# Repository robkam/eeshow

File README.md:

# eeshow
Eeshow - Eeschema schematics renderer and viewer, a tool to ease KiCad schematic file navigation.

Forked from http://neo900.org/stuff/eeshow/.

See https://github.com/robkam/eeshow/wiki for more info.

In the transition between KiCad 4 and KiCad 5 the savefiles format has changed the way libraries are looked up. So Eeshow now needs an update to support both versions.

This work is distributed under the terms of the GNU GENERAL PUBLIC LICENSE, Version 2.

Folder eeshow is eeshow.

Folder ee is the Neo900 schematics, refered to as an example in the wiki.

Folder img is images for the wiki.

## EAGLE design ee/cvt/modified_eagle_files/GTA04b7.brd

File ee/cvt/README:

Conversion session transcript
=============================

git clone https://github.com/lachlanA/eagle-to-kicad.git
mkdir <base-directory>
cd <base-directory>
mkdir eagle
cp ../gdc/sep18/* eagle
mkdir cvt

Some of the following interactions are timestamped, to indicate roughly
when to expect interactions. The timestamps are [minutes:seconds] of
total CPU time of the "eagle" process on a Q6600.

Note: it is best not type anything else during the conversion, especially
around the time when new dialogs may pop up. The Eagle pop-ups will appear
unannounced and grab the input focus. Keystrokes will therefore end up in
Eagle dialogs, changing inputs.

- open schematics in Eagle

File > Run ULP (.../eagle-to-kicad/renumber-sheet.ulp)
- set script path to .../eagle-to-kicad/
- set output directory (.../cvt/)

[10:54] "This ULP will change unconnected VIA's to PADS"
- accept defaults

[11:01] "Consult log file for unncontded via's and tracks"
/home/n9/ee/cvt/GTA04b7_conversion_log.txt
- 1469 unconnected tracks
- 6 unconnected vias
- accept

[11:01] /home/n9/ee/cvt/modified_eagle_files/GTA04b7~fix_via_hack.scr, Line 85:
The Light edition of EAGLE can't perform the requested action!
You can't add parts to this sheet.
- accept
- idem, lines 89, 93, 97, 101, 105. accept.

[11:04] Unknown element VP_0
line 11889
- accept
- idem, VP_1, VP_2, VP_3, VP_4, VP_5. accept.

[11:10] Large dialog
- Output: set all sheet sizes to A3
- Sheet size: set to A3
- accept

[32:11] Library dialog
- Accept (note: dialog stays open after clicking "OK")

[33:21] "There were Errors during the export please read the log for more
	 information"
- Accept

[33:44] /home/n9/ee/cvt/GTA04b7.scr, Line 31320:
Package SOT223-6 doesn't have enough pads for
all 10 pins of device TPS73733
- accept

[33:44] /home/n9/ee/cvt/GTA04b7.scr, Line 31321:
Use the PACKAGE command to select a package variant first
- accept
- idem, lines 31322 to 31326. Accept.

[33:46] Output ... dialog.
- accept defaults

[33:55] There are: 217 missing part prefix(s).
	Conversion finished!
- accept

[33:56] Log file dialog
- accept

Common issues in converted schematics
=====================================

Component text size
-------------------

Component text (component reference, value, etc.), should have a size
of 50 mil. The converted schematics frequently use 45 mil or 70 mil.

KiCad stores the default size, location, and alignment of text fields
in the definition of the schematics symbol ("component", .lib). This
is copied into the schematics when placing a symbol, and can then be
modified individually for each use of the symbol.

To change a symbol in the library, right-click on the symbol in the
schematics, Edit component > Edit with Library Editor
Make the changes in the component editor. Important: make sure that
all pins are aligned with a 50 mil grid. To abort changes, simply
quit the component editor. To save changes, click
Update current component in current library
followed by
Save current library to disk

Eeschema will pick up changes in geometry and fixed text automatically,
but it will not change fields of existing symbols. To update fields to
the definitions in the library, press E to edit the component, then
click Reset to Library Defaults.

Component text alignment
------------------------

Many text fields in the converted schematics are vertically aligned
with the bottom of the text. It is often more convenient to align with
the center, such that a field can be placed near a wire (or anything
else that follows the 50 mil grid) without getting too close.

Pin types
---------

Some pin types in the converted schematics are incorrect or at least
unusual. In general, passive components like LED should have their
terminals marked as "passive", not as "power input" or such.

Pin types can only be corrected by changing the component in the
library.

Label text size
---------------

Many labels have (or had) a text size of 65 mil. This makes global
labels overlap when stacked with 100 mil spacing. The text size can
be changed by pressing "E" on the label.

Label type and direction
------------------------

Labels that should be global were converted to local. To change them
back to global, right-click, Change type > Change to Global Label

In KiCad, global and hierarchical labels (but not local labels)
indicate a direction. This can be changed by pressing "E" on the global
label.

Tiny labels
-----------

The converter flags each net with a tiny label (10 mil), to ensure the
net is really what Eagle said it was. Most of these labels have already
been removed, but some remain.

In general, all such labels should be deleted. Since they can sometimes
indicate conflicts in the design (cf. VBUS), one should check, before
deleting, that they are consistent with the net that is expected to be
at this location.

Power flag
----------

KiCad requires all nets that are used as power input to be driven by a
power output (i.e., a pin marked as such). If a net has no implicit
power source (e.g., if it is separated from a power output by a choke),
the POWERED symbol (which is a single-pin power output) has to be placed
on the net. (POWERED is a nicer form of PWR_FLAG from the default KiCad
library.)

Unusual wiring
--------------

The "normal" drawing style in KiCad is that pins are connected by a
single wire that continues for at least 50 mil, better 100 mil, in the
direction of the pin. This wire can then bend, form T-joints with other
wires, etc.

The converted schematics contain a large number of wires that are
perpendicular to the pin they connect to, and some pins are even
connected directly, without wire. While this "works", it often looks
confusing and it complicates moving or dragging items. The best way to
resolve such issues is often to just delete the wires and junctions of
the net in question, move components to create a bit more room, then
redraw the net.

Caution: deleting a wire often deletes the entire wire, across
junctions. Checking the result of major reconstruction against a PDF
taken from the original state (or the Eagle original) is recommended.

Unifying multi-unit components
------------------------------

Some components are drawn as consisting of a very large number of
units. E.g., the rather simple digital microphones had no less than
five units each.

A quick way to reduce the number of units is to invoke the component
editor on the component, setting the pins in units B and above to
"Common to all units in component", reducing the number of units in
"Edit component properties" to one, and finally arranging the pins in
a suitable pattern.

Oversized arcs
--------------

KiCad arcs can be either clockwise or counter-clockwise, and there is
no explicit indication of the direction. To avoid ambiguities, arcs are
limited to < 180 degrees. The converter seems to be unaware of this
restriction and produces arcs >= 180 degrees. (Even when drawing an arc
of 180 degrees in KiCad, it is saved with a start and end angle of 0.1
and 179.9 degrees, respectively.)

To fix this, oversized each arc needs to be broken into two (or more)
smaller arcs.

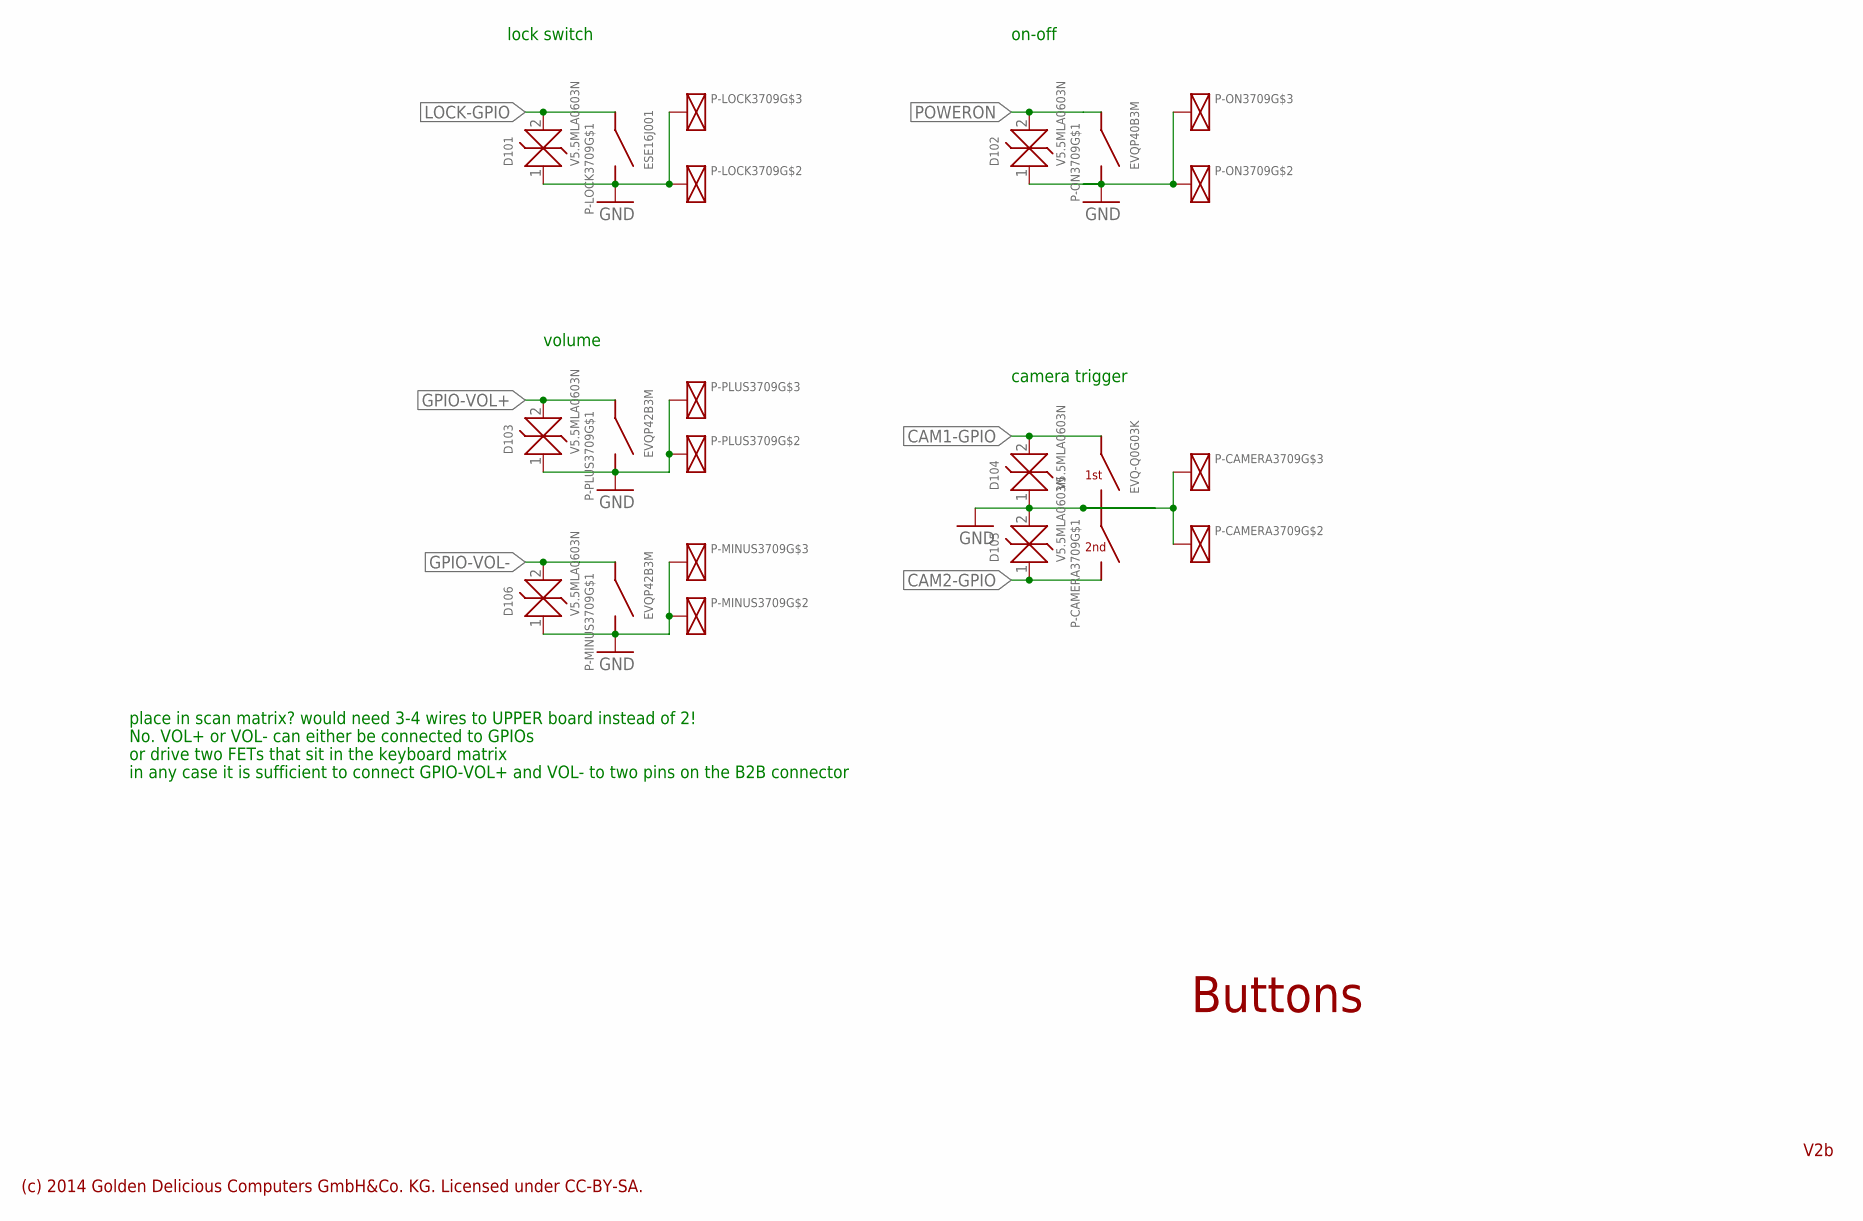
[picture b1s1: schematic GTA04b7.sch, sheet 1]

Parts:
D101, D102, D103, D104, D105, D106: V5.5MLA0603N; SMD-0603
P-CAMERA3709: EVQ-Q0G03K; EVQQ0
P-LOCK3709: ESE16J001; ESE-16J001
P-MINUS3709: EVQP42B3M; EVQP40B3M
P-ON3709: EVQP40B3M
P-PLUS3709: EVQP42B3M; EVQP40B3M

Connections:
CAM1-GPIO: D104.2 (K), P-CAMERA3709.1
CAM2-GPIO: D105.1 (A), P-CAMERA3709.2
GND: D101.1 (A), D102.1 (A), D103.1 (A), D104.1 (A), D105.2 (K), D106.1 (A), P-CAMERA3709.3, P-CAMERA3709.S1 (SHIELD), P-CAMERA3709.S2 (SHIELD), P-LOCK3709.2 (SHIELD), P-LOCK3709.3 (B), P-LOCK3709.4 (SHIELD), P-MINUS3709.2 (B), P-MINUS3709.S1 (SHIELD), P-MINUS3709.S2 (SHIELD), P-ON3709.2 (B), P-ON3709.S1 (SHIELD), P-ON3709.S2 (SHIELD), P-PLUS3709.2 (B), P-PLUS3709.S1 (SHIELD), P-PLUS3709.S2 (SHIELD); also elsewhere on the board
GPIO-VOL+: D103.2 (K), P-PLUS3709.1 (A)
GPIO-VOL-: D106.2 (K), P-MINUS3709.1 (A)
LOCK-GPIO: D101.2 (K), P-LOCK3709.1 (A)
POWERON: D102.2 (K), P-ON3709.1 (A)

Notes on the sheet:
Buttons
(c) 2014 Golden Delicious Computers GmbH&Co. KG. Licensed under CC-BY-SA.
lock switch
on-off
volume
camera trigger
place in scan matrix? would need 3-4 wires to UPPER board instead of 2!
No. VOL+ or VOL- can either be connected to GPIOs
or drive two FETs that sit in the keyboard matrix
in any case it is sufficient to connect GPIO-VOL+ and VOL- to two pins on the B2B connector
V2b

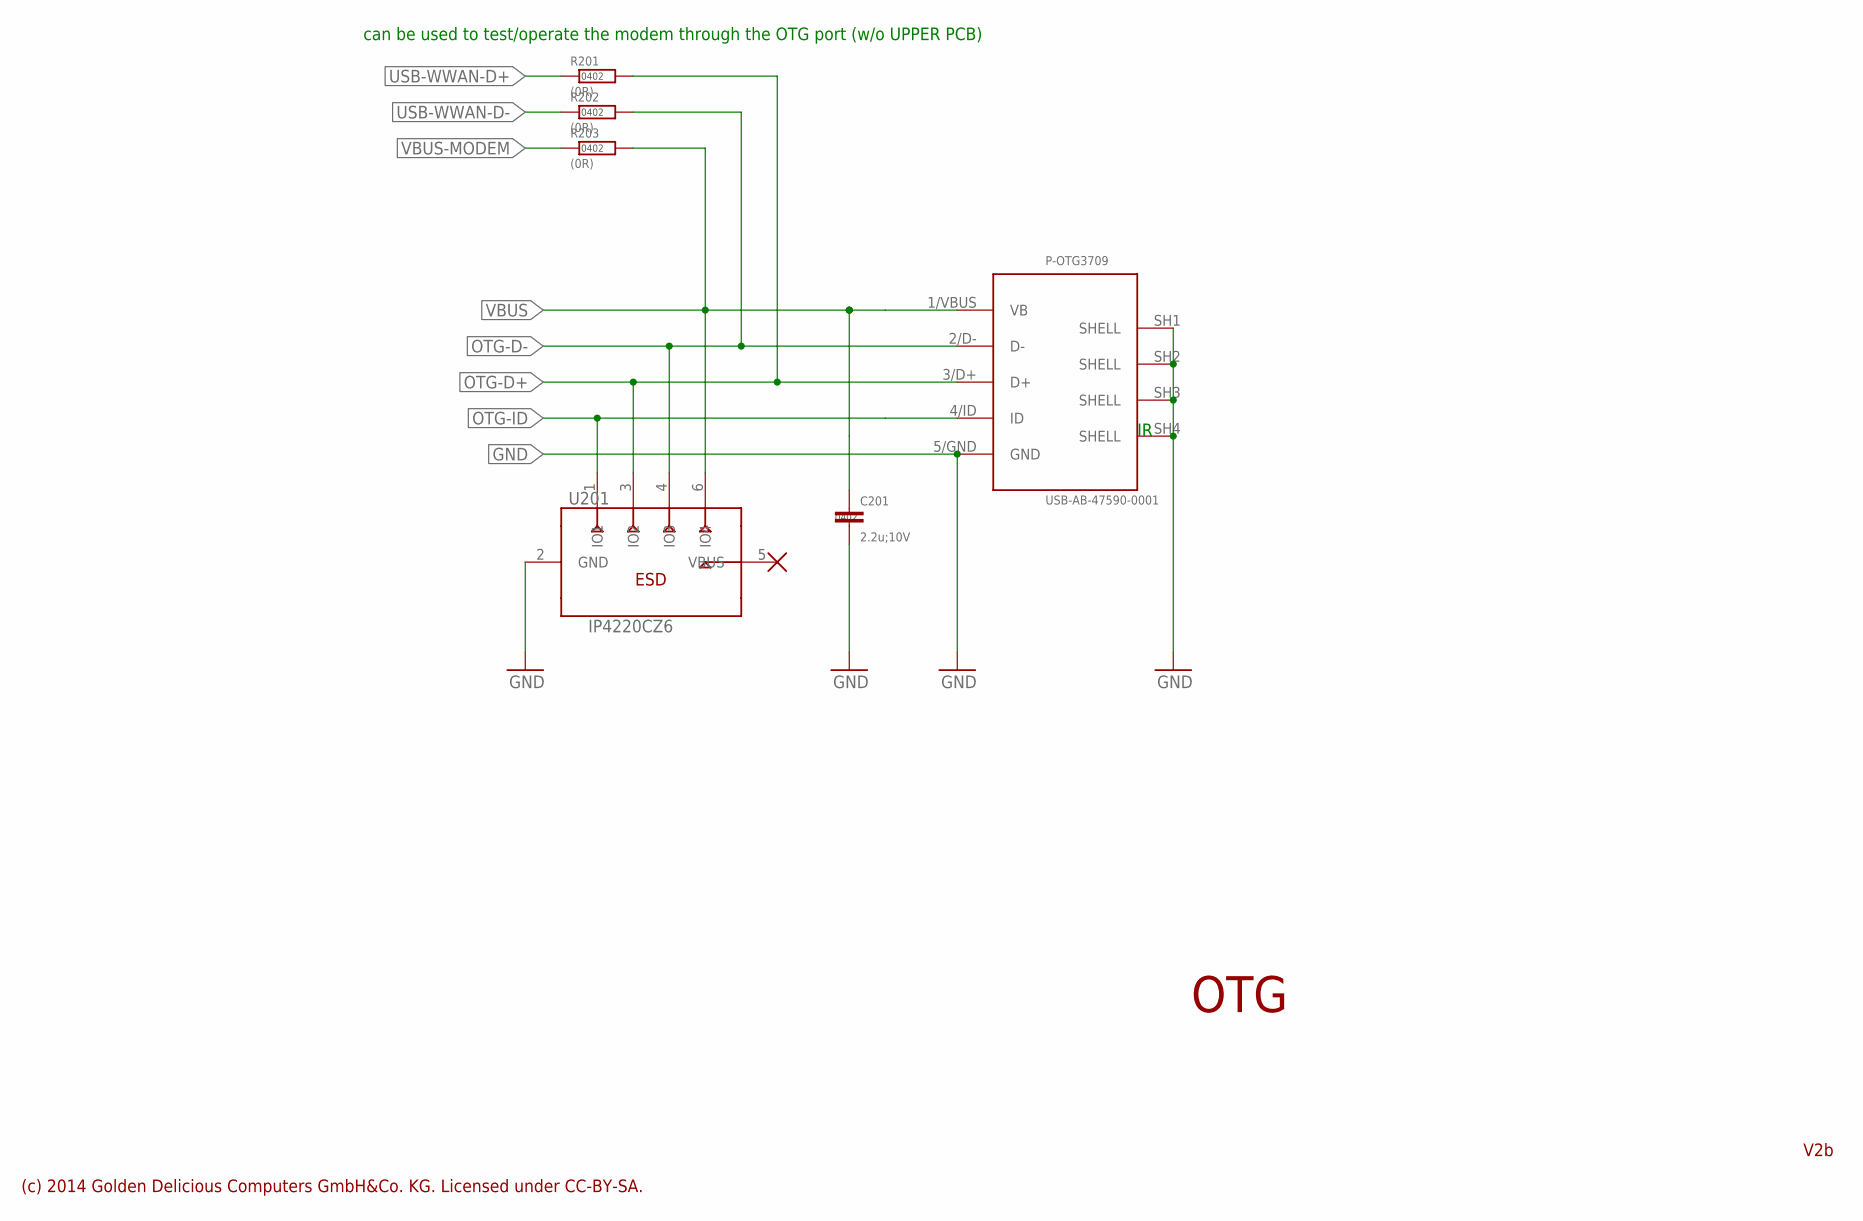
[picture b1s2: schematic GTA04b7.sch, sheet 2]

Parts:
C201: 2.2u;10V; SMD-0402
P-OTG3709: USB-AB-47590-0001; SD-47590-0001
R201, R202, R203: (0R); SMD-0402
U201: IP4220CZ6; SOT457-6

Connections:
GND: C201.2, P-OTG3709.5/GND (GND), P-OTG3709.SH1 (SHELL), P-OTG3709.SH2 (SHELL), P-OTG3709.SH3 (SHELL), P-OTG3709.SH4 (SHELL), U201.2 (GND); also elsewhere on the board
OTG-D+: P-OTG3709.3/D+ (D+), R201.2, U201.3 (IO2); also elsewhere on the board
OTG-D-: P-OTG3709.2/D- (D-), R202.2, U201.4 (IO3); also elsewhere on the board
OTG-ID: P-OTG3709.4/ID (ID), U201.1 (IO1)
USB-WWAN-D+: R201.1; also elsewhere on the board
USB-WWAN-D-: R202.1; also elsewhere on the board
VBUS: C201.1, P-OTG3709.1/VBUS (VB), U201.6 (IO4); also elsewhere on the board
VBUS-MODEM: R203.1; also elsewhere on the board
VBUS-MODEM-CPU: R203.2; also elsewhere on the board

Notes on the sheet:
(c) 2014 Golden Delicious Computers GmbH&Co. KG. Licensed under CC-BY-SA.
OTG
V2b
can be used to test/operate the modem through the OTG port (w/o UPPER PCB)

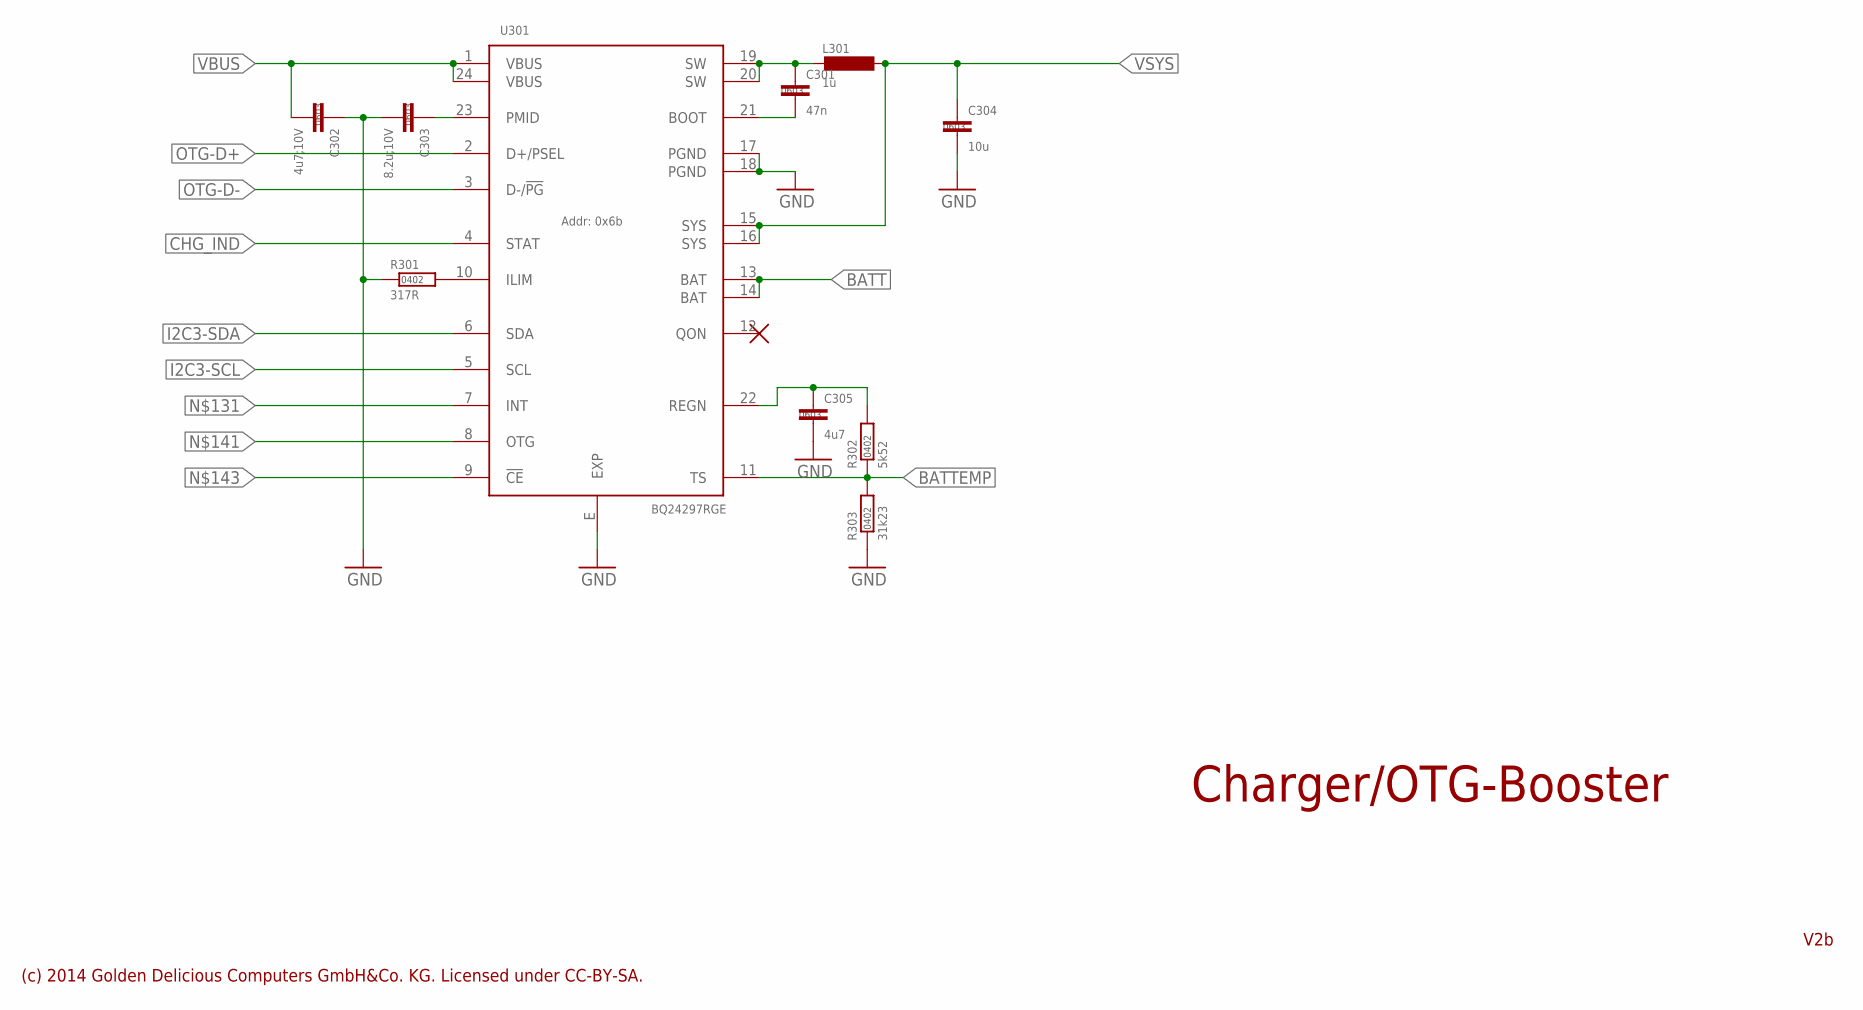
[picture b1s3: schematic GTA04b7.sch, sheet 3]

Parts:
C301: 47n; SMD-0603
C302: 4u7;10V; SMD-0603
C303: 8.2u;10V; SMD-0603
C304: 10u; SMD-0603
C305: 4u7; SMD-0603
L301: 1u; SMD-1212
R301: 317R; SMD-0402
R302: 5k52; SMD-0402
R303: 31k23; SMD-0402
U301: BQ24297RGE; S-PVQFN-N24-0.5

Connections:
BATT: U301.13 (BAT), U301.14 (BAT); also elsewhere on the board
BATTEMP: R302.1, R303.2, U301.11 (TS); also elsewhere on the board
CHG_IND: U301.4 (STAT); also elsewhere on the board
GND: C302.1, C303.2, C304.2, C305.2, R301.1, R303.1, U301.17 (PGND), U301.18 (PGND), U301.E (EXP); also elsewhere on the board
I2C3-SCL: U301.5 (SCL); also elsewhere on the board
I2C3-SDA: U301.6 (SDA); also elsewhere on the board
unnamed: C303.1, U301.23 (PMID)
unnamed: C305.1, R302.2, U301.22 (REGN)
unnamed: C301.1, L301.2, U301.19 (SW), U301.20 (SW)
unnamed: R301.2, U301.10 (ILIM)
unnamed: C301.2, U301.21 (BOOT)
OTG-D+: U301.2 (D+/PSEL); also elsewhere on the board
OTG-D-: U301.3 (D-/!PG); also elsewhere on the board
VBUS: C302.2, U301.1 (VBUS), U301.24 (VBUS); also elsewhere on the board
VSYS: C304.1, L301.1, U301.15 (SYS), U301.16 (SYS); also elsewhere on the board

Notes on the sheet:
(c) 2014 Golden Delicious Computers GmbH&Co. KG. Licensed under CC-BY-SA.
Charger/OTG-Booster
V2b

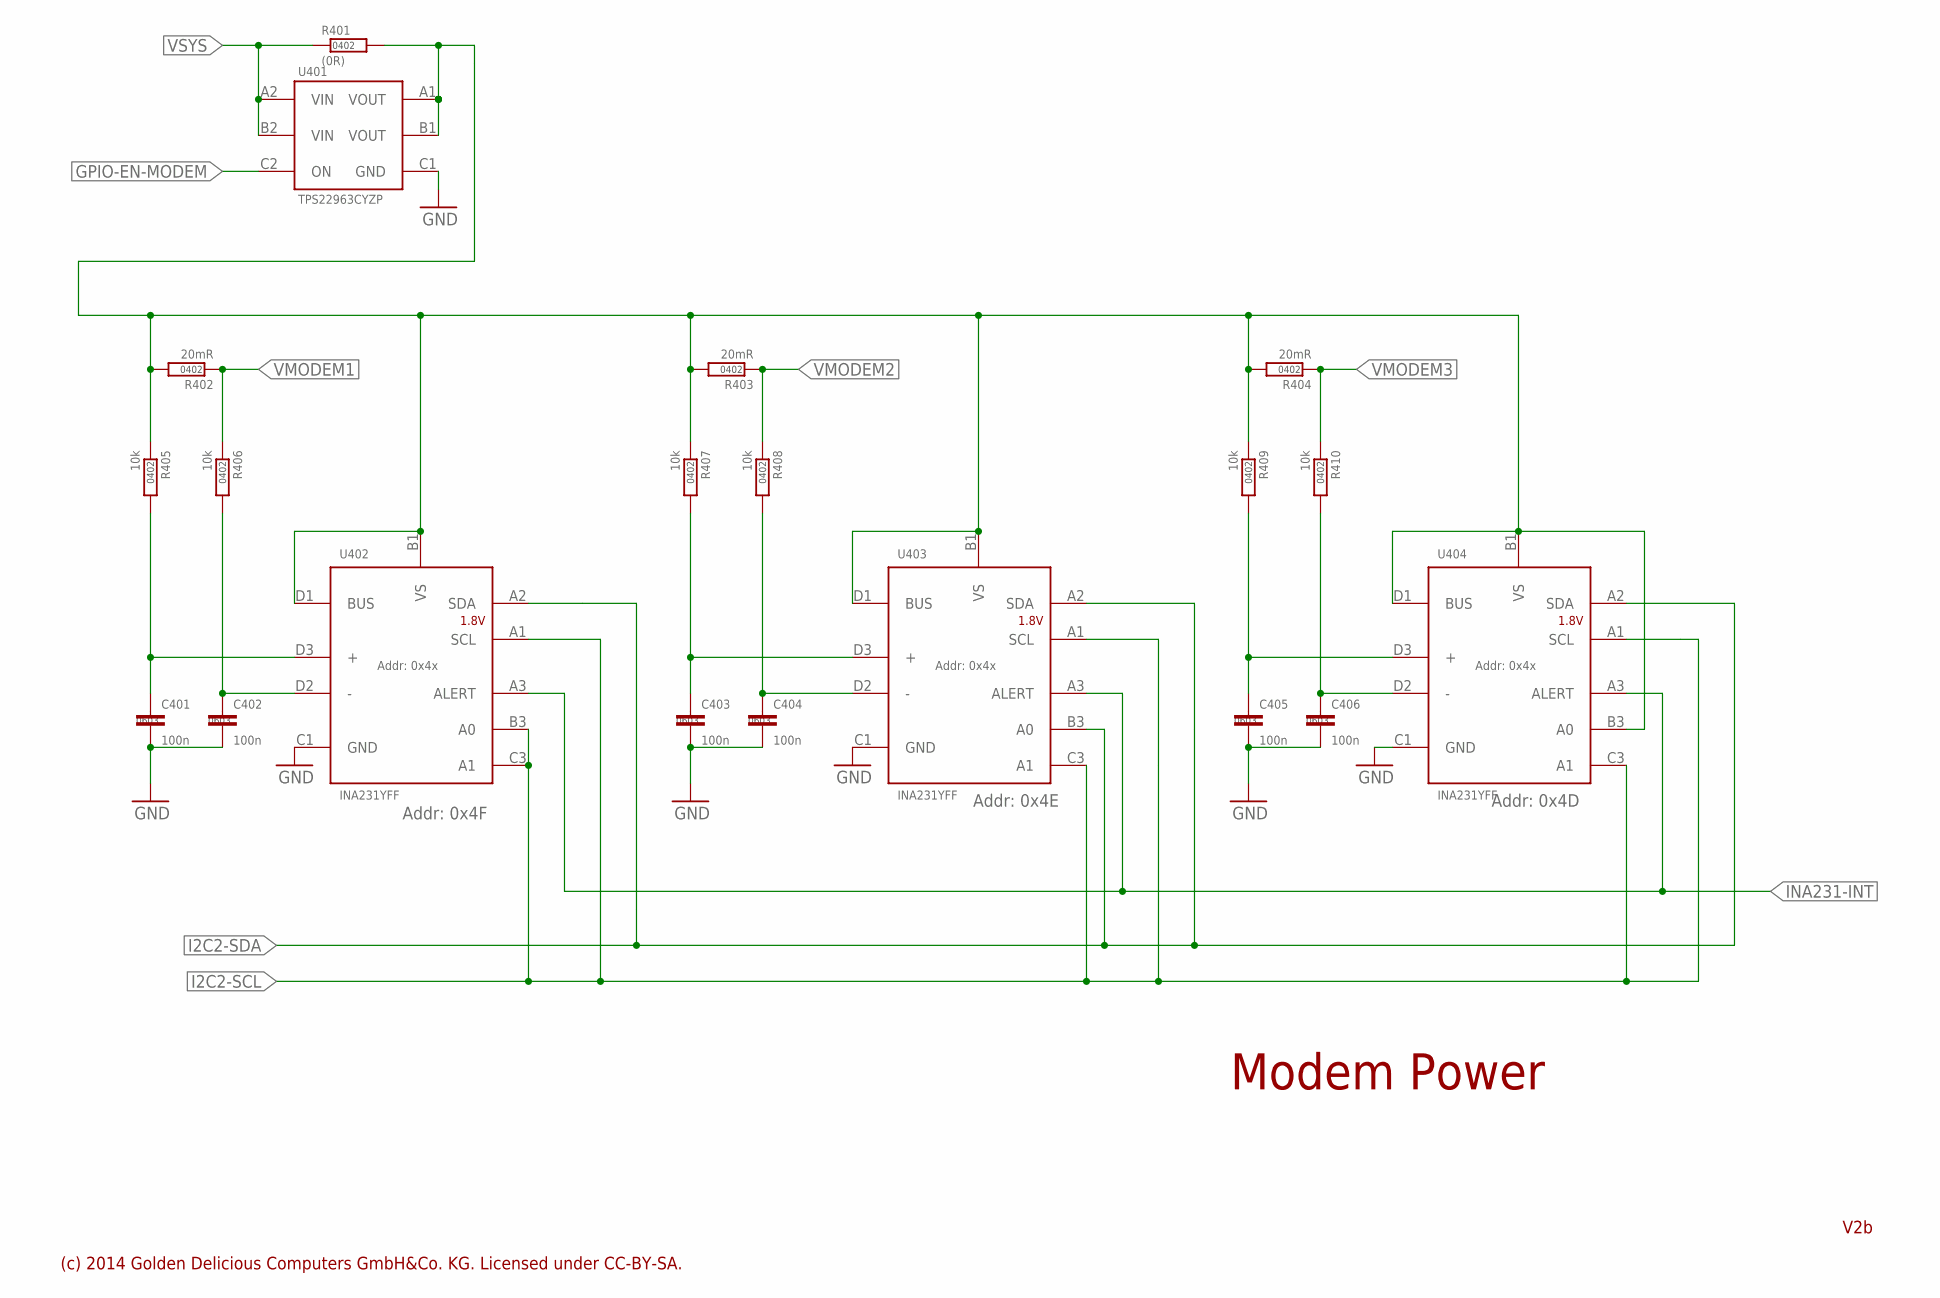
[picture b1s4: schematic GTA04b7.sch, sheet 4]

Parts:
C401, C402, C403, C404, C405, C406: 100n; SMD-0603
R401: (0R); SMD-0402
R402, R403, R404: 20mR; SMD-0402
R405, R406, R407, R408, R409, R410: 10k; SMD-0402
U401: TPS22963CYZP; R-XBGA-N6-0.5
U402, U403, U404: INA231YFF; R-XBGA-N12-0.4

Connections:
GND: C401.2, C402.2, C403.2, C404.2, C405.2, C406.2, U401.C1 (GND), U402.C1 (GND), U403.C1 (GND), U404.C1 (GND); also elsewhere on the board
GPIO-EN-MODEM: U401.C2 (ON)
I2C2-SCL: U402.A1 (SCL), U402.B3 (A0), U402.C3 (A1), U403.A1 (SCL), U403.C3 (A1), U404.A1 (SCL), U404.C3 (A1); also elsewhere on the board
I2C2-SDA: U402.A2 (SDA), U403.A2 (SDA), U403.B3 (A0), U404.A2 (SDA); also elsewhere on the board
INA231-INT: U402.A3 (ALERT), U403.A3 (ALERT), U404.A3 (ALERT)
unnamed: C403.1, R407.2, U403.D3 (+)
unnamed: C404.1, R408.2, U403.D2 (-)
unnamed: C405.1, R409.2, U404.D3 (+)
unnamed: C406.1, R410.2, U404.D2 (-)
unnamed: R401.2, R402.2, R403.2, R404.2, R405.1, R407.1, R409.1, U401.A1 (VOUT), U401.B1 (VOUT), U402.B1 (VS), U402.D1 (BUS), U403.B1 (VS), U403.D1 (BUS), U404.B1 (VS), U404.D1 (BUS)
unnamed: C401.1, R405.2, U402.D3 (+)
unnamed: C402.1, R406.2, U402.D2 (-)
VMODEM1: R402.1, R406.1; also elsewhere on the board
VMODEM2: R403.1, R408.1; also elsewhere on the board
VMODEM3: R404.1, R410.1; also elsewhere on the board
VSYS: R401.1, U401.A2 (VIN), U401.B2 (VIN); also elsewhere on the board

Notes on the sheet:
(c) 2014 Golden Delicious Computers GmbH&Co. KG. Licensed under CC-BY-SA.
Modem Power
Addr: 0x4F
Addr: 0x4E
Addr: 0x4D
V2b

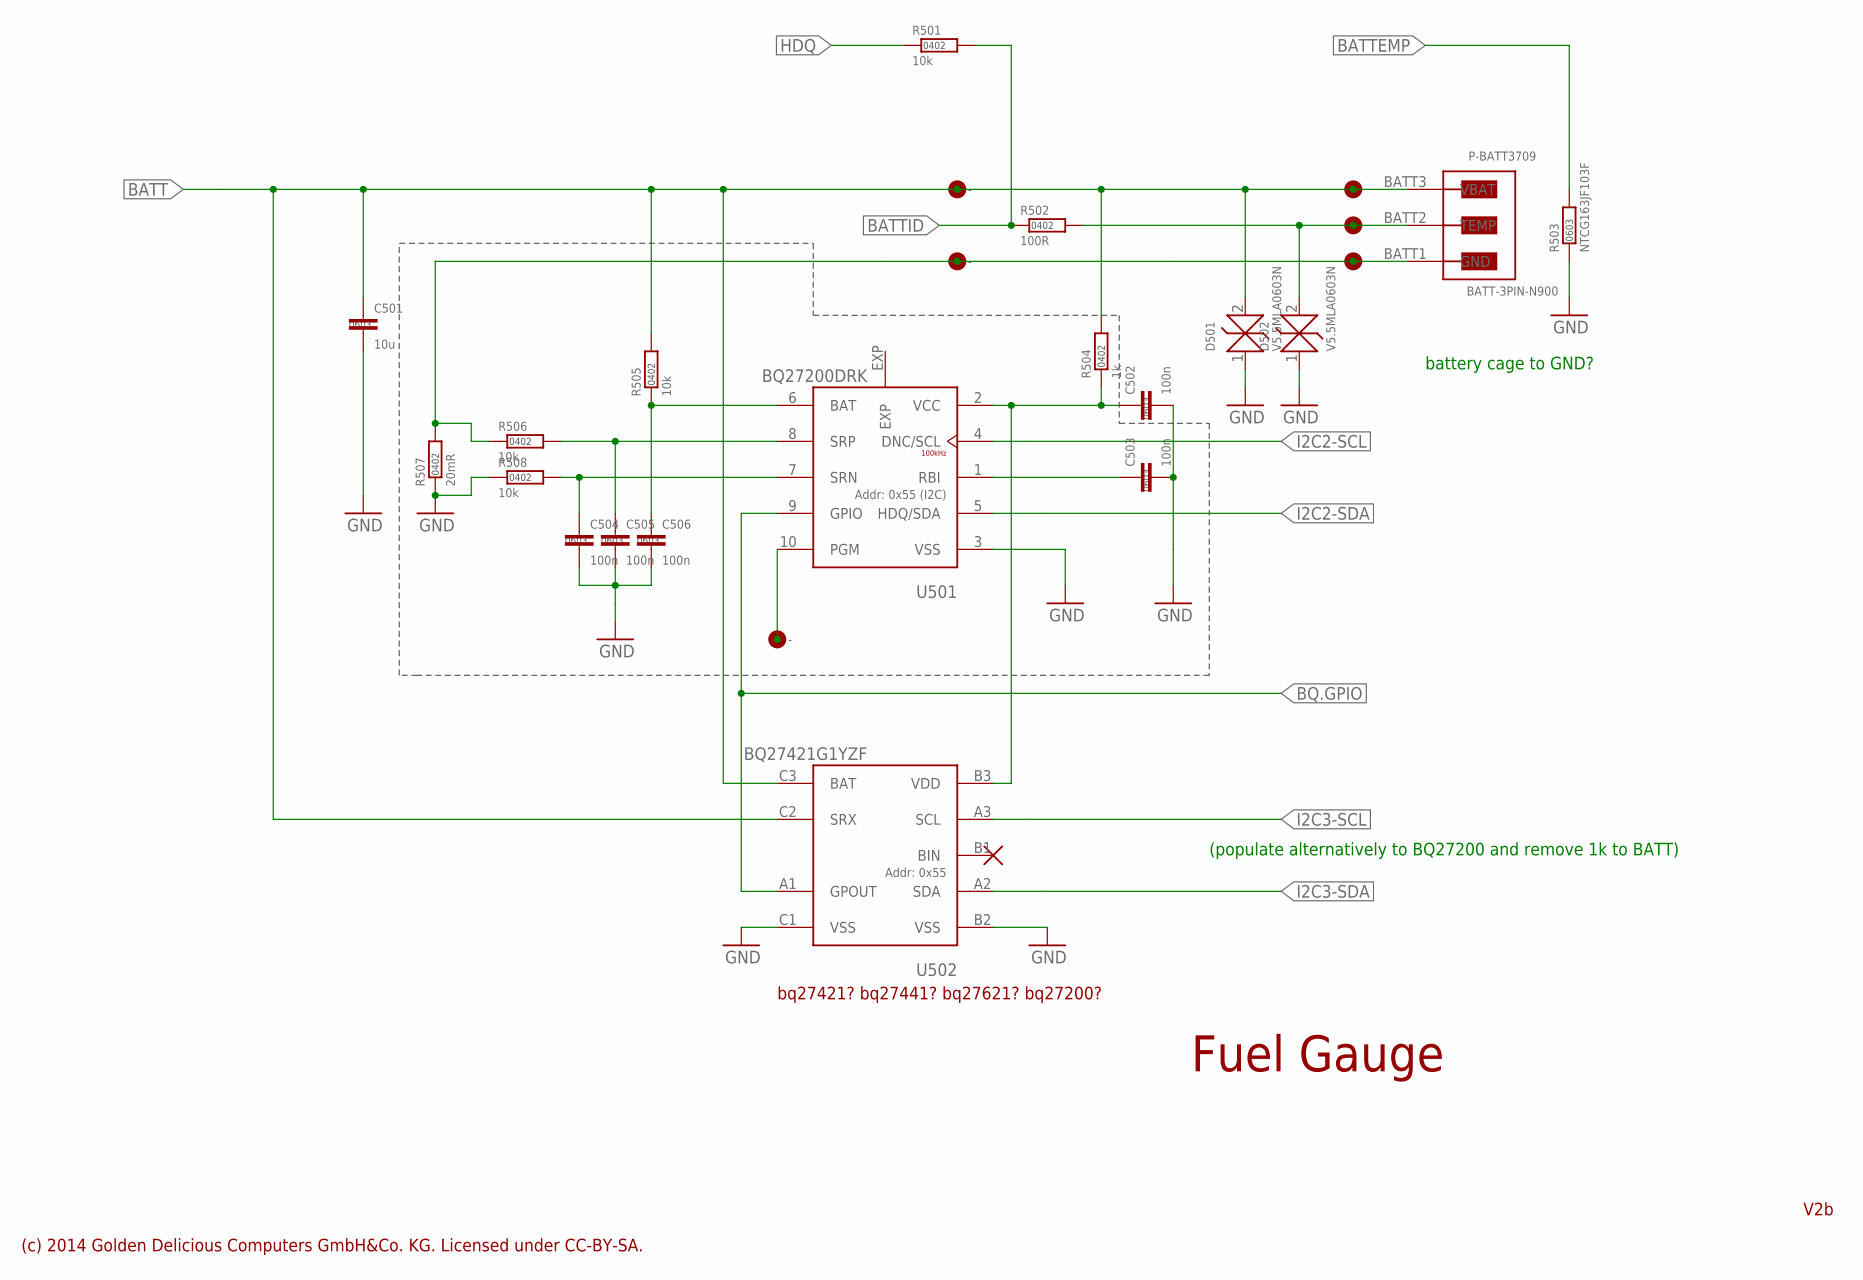
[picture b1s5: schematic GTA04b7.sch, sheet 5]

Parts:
BATT+3709: TEST-POINT-1.25; TP-1.25
BATT-GND3709: TEST-POINT-1.25; TP-1.25
BATT-ID3709: TEST-POINT-1.25; TP-1.25
BGND3709: -; 1PIN-HOLE
C501: 10u; SMD-0603
C502, C503, C504, C505, C506: 100n; SMD-0603
D501, D502: V5.5MLA0603N; SMD-0603
P-BATT3709: BATT-3PIN-N900; N900-BATTCONN
PGM3709: -; 1PIN-HOLE
R501, R505, R506, R508: 10k; SMD-0402
R502: 100R; SMD-0402
R503: NTCG163JF103F; SMD-0603
R504: 1k; SMD-0402
R507: 20mR; SMD-0402
U501: BQ27200DRK; S-PVSON-N10-4X3
U502: BQ27421G1YZF; S-XBGA-N9-0.5
VBATT3709: -; 1PIN-HOLE

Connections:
BATT: BATT+3709.P, C501.1, D501.2 (K), P-BATT3709.BATT3 (VBAT), R504.2, R505.2, U502.C2 (SRX), U502.C3 (BAT), VBATT3709.P$1; also elsewhere on the board
BATTEMP: R503.2; also elsewhere on the board
BATTID: R501.2, R502.1
BGND: BATT-GND3709.P, BGND3709.P$1, P-BATT3709.BATT1 (GND), R506.1, R507.2
BQ.GPIO: U501.9 (GPIO), U502.A1 (GPOUT); also elsewhere on the board
EXP: U501.EXP
GND: C501.2, C502.2, C503.2, C504.2, C505.2, C506.2, D501.1 (A), D502.1 (A), R503.1, R507.1, R508.1, U501.3 (VSS), U502.B2 (VSS), U502.C1 (VSS); also elsewhere on the board
HDQ: R501.1
I2C2-SCL: U501.4 (DNC/SCL); also elsewhere on the board
I2C2-SDA: U501.5 (HDQ/SDA); also elsewhere on the board
I2C3-SCL: U502.A3 (SCL); also elsewhere on the board
I2C3-SDA: U502.A2 (SDA); also elsewhere on the board
unnamed: BATT-ID3709.P, D502.2 (K), P-BATT3709.BATT2 (TEMP), R502.2
unnamed: C503.1, U501.1 (RBI)
unnamed: C505.1, R506.2, U501.8 (SRP)
unnamed: C506.1, R505.1, U501.6 (BAT)
unnamed: C504.1, R508.2, U501.7 (SRN)
unnamed: PGM3709.P$1, U501.10 (PGM)
unnamed: C502.1, R504.1, U501.2 (VCC), U502.B3 (VDD)

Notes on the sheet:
(c) 2014 Golden Delicious Computers GmbH&Co. KG. Licensed under CC-BY-SA.
Fuel Gauge
battery cage to GND?
bq27421? bq27441? bq27621? bq27200?
(populate alternatively to BQ27200 and remove 1k to BATT)
V2b

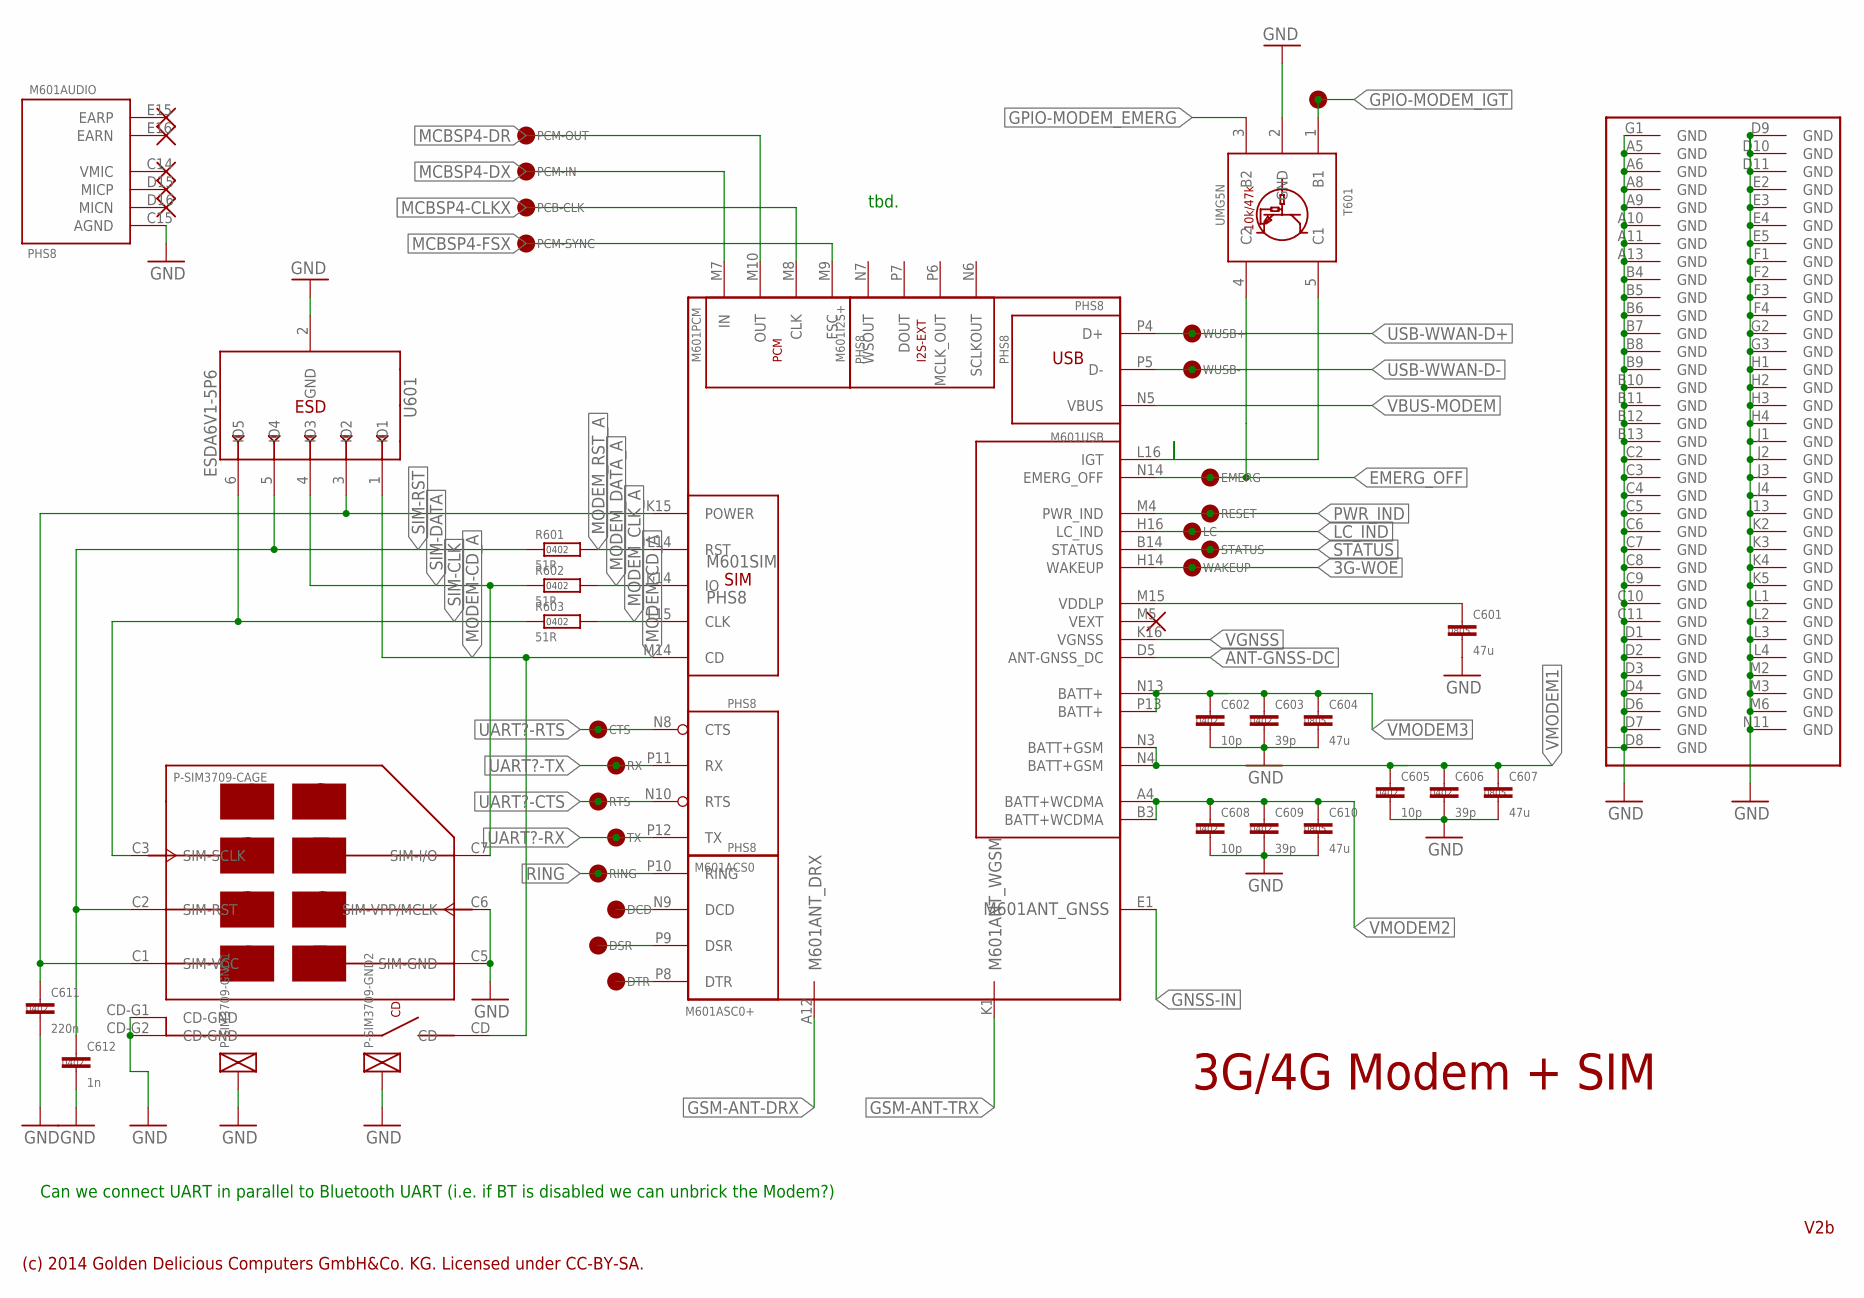
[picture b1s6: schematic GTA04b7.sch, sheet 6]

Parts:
C601, C604, C607, C610: 47u; SMD-0805
C602, C605, C608: 10p; SMD-0402
C603, C606, C609: 39p; SMD-0402
C611: 220n; SMD-0402
C612: 1n; SMD-0402
CTS3709: CTS; TP-0.75
D+3709: WUSB+; TP-1.25
D-3709: WUSB-; TP-1.25
DCD3709: DCD; TP-0.75
DSR3709: DSR; TP-0.75
DTR3709: DTR; TP-0.75
GPIO601: TEST-POINT-1.25; TP-1.25
LC_IND3709: LC; TP-1.25
M601: PHS8; P*S8
MCBSP4-CLK3709: PCB-CLK; TP-1.25
MCBSP4-DR3709: PCM-OUT; TP-1.25
MCBSP4-DX3709: PCM-IN; TP-1.25
MCBSP4-FSX3709: PCM-SYNC; TP-1.25
P-SIM3709: SIM-SLOT-6PIN+CD-CHECK-PINS; SJ106220
PWR_IND3709: RESET; TP-1.25
R601, R602, R603: 51R; SMD-0402
RING3709: RING; TP-0.75
RTS3709: RTS; TP-0.75
RX3709: RX; TP-0.75
STATUS3709: STATUS; TP-1.25
T601: UMG5N; SC88A
TP2: EMERG; TP-1.25
TX3709: TX; TP-0.75
U601: ESDA6V1-5P6; SOT666IP
WAKEUP3709: WAKEUP; TP-1.25

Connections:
3G-WOE: M601.H14 (WAKEUP), WAKEUP3709.P
ANT-GNSS-DC: M601.D5 (ANT-GNSS_DC); also elsewhere on the board
EMERG_OFF: M601.N14 (EMERG_OFF), T601.4 (C2), TP2.P
GND: C601.2, C602.2, C603.2, C604.2, C605.2, C606.2, C607.2, C608.2, C609.2, C610.2, C611.2, C612.2, M601.A5 (GND), M601.A6 (GND), M601.A8 (GND), M601.A9 (GND), M601.A10 (GND), M601.A11 (GND), M601.A13 (GND), M601.B4 (GND), M601.B5 (GND), M601.B6 (GND), M601.B7 (GND), M601.B8 (GND), M601.B9 (GND), M601.B10 (GND), M601.B11 (GND), M601.B12 (GND), M601.B13 (GND), M601.C2 (GND), M601.C3 (GND), M601.C4 (GND), M601.C5 (GND), M601.C6 (GND), M601.C7 (GND), M601.C8 (GND), M601.C9 (GND), M601.C10 (GND), M601.C11 (GND), M601.C15 (AGND), M601.D1 (GND), M601.D2 (GND), M601.D3 (GND), M601.D4 (GND), M601.D6 (GND), M601.D7 (GND), M601.D8 (GND), M601.D9 (GND), M601.D10 (GND), M601.D11 (GND), M601.E2 (GND), M601.E3 (GND), M601.E4 (GND), M601.E5 (GND), M601.F1 (GND), M601.F2 (GND), M601.F3 (GND), M601.F4 (GND), M601.G1 (GND), M601.G2 (GND), M601.G3 (GND), M601.H1 (GND), M601.H2 (GND), M601.H3 (GND), M601.H4 (GND), M601.J1 (GND), M601.J2 (GND), M601.J3 (GND), M601.J4 (GND), M601.J13 (GND), M601.K2 (GND), M601.K3 (GND), M601.K4 (GND), M601.K5 (GND), M601.L1 (GND), M601.L2 (GND), M601.L3 (GND), M601.L4 (GND), M601.M2 (GND), M601.M3 (GND), M601.M6 (GND), M601.N11 (GND), P-SIM3709.C5 (SIM-GND), P-SIM3709.C6 (SIM-VPP/MCLK), P-SIM3709.CD-G1 (CD-GND), P-SIM3709.CD-G2 (CD-GND), P-SIM3709.S1 (SHIELD), P-SIM3709.S2 (SHIELD), T601.2 (GND), U601.2 (GND); also elsewhere on the board
GNSS-IN: M601.E1 (PIN); also elsewhere on the board
GPIO-MODEM_EMERG: T601.3 (B2)
GPIO-MODEM_IGT: GPIO601.P, T601.1 (B1)
GSM-ANT-DRX: M601.A12 (PIN); also elsewhere on the board
GSM-ANT-TRX: M601.K1 (PIN); also elsewhere on the board
LC_IND: LC_IND3709.P, M601.H16 (LC_IND)
MCBSP4-CLKX: M601.M8 (CLK), MCBSP4-CLK3709.P
MCBSP4-DR: M601.M10 (OUT), MCBSP4-DR3709.P
MCBSP4-DX: M601.M7 (IN), MCBSP4-DX3709.P
MCBSP4-FSX: M601.M9 (FSC), MCBSP4-FSX3709.P
MODEM-CD_A: M601.M14 (CD), P-SIM3709.CD, U601.1 (IO1); also elsewhere on the board
MODEM_CLK_A: M601.L15 (CLK), R603.2; also elsewhere on the board
MODEM_DATA_A: M601.K14 (IO), R602.2; also elsewhere on the board
MODEM_RST_A: M601.L14 (RST), R601.2; also elsewhere on the board
unnamed: C611.1, M601.K15 (POWER), P-SIM3709.C1 (SIM-VCC), U601.3 (IO2)
unnamed: DCD3709.P, M601.N9 (DCD)
unnamed: DSR3709.P, M601.P9 (DSR)
unnamed: DTR3709.P, M601.P8 (DTR)
unnamed: C601.1, M601.M15 (VDDLP)
ON_KEY: M601.L16 (IGT), T601.5 (C1)
PWR_IND: M601.M4 (PWR_IND), PWR_IND3709.P
RING: M601.P10 (RING), RING3709.P
SIM-CLK: P-SIM3709.C3 (SIM-SCLK), R603.1, U601.6 (IO5); also elsewhere on the board
SIM-DATA: P-SIM3709.C7 (SIM-I/O), R602.1, U601.4 (IO3); also elsewhere on the board
SIM-RST: C612.1, P-SIM3709.C2 (SIM-RST), R601.1, U601.5 (IO4); also elsewhere on the board
STATUS: M601.B14 (STATUS), STATUS3709.P
UART?-CTS: M601.N10 (RTS), RTS3709.P
UART?-RTS: CTS3709.P, M601.N8 (CTS)
UART?-RX: M601.P12 (TX), TX3709.P
UART?-TX: M601.P11 (RX), RX3709.P
USB-WWAN-D+: D+3709.P, M601.P4 (D+); also elsewhere on the board
USB-WWAN-D-: D-3709.P, M601.P5 (D-); also elsewhere on the board
VBUS-MODEM: M601.N5 (VBUS); also elsewhere on the board
VEXT: M601.M5 (VEXT)
VGNSS: M601.K16 (VGNSS); also elsewhere on the board
VMODEM1: C605.1, C606.1, C607.1, M601.N3 (BATT+GSM), M601.N4 (BATT+GSM); also elsewhere on the board
VMODEM2: C608.1, C609.1, C610.1, M601.A4 (BATT+WCDMA), M601.B3 (BATT+WCDMA); also elsewhere on the board
VMODEM3: C602.1, C603.1, C604.1, M601.N13 (BATT+), M601.P13 (BATT+); also elsewhere on the board

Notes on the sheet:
3G/4G Modem + SIM
(c) 2014 Golden Delicious Computers GmbH&Co. KG. Licensed under CC-BY-SA.
V2b
tbd.
Can we connect UART in parallel to Bluetooth UART (i.e. if BT is disabled we can unbrick the Modem?)
